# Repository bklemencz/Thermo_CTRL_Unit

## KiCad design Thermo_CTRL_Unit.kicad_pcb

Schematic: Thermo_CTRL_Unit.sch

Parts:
C1: 1u; C_0805
C2, C5, C7, C8, C9: 100n; C_0805
C3, C4: 22p; C_0805
C6: 10u; C_0805
C10, C13: 10uF; C_1206
C11: 100nF; C_0805
C12: 1uF; C_1206
D1, D2, D3: Red; LED_0805
D4: Green; LED_0805
D5: TL431; SOT-23
D6: SS13; SMA_Standard
FB1: FB_SMD_0805; R_0805
IC1: ATMEGA168PA-A; TQFP-32_7x7mm_Pitch0.8mm
J1: RJ12; RJ12_2mm_Pitch
P1: SW_TH1; JST_B3B-XH-A
P2: ISCP; Pin_Header_Straight_2x03
P3: SW_TH2; JST_B3B-XH-A
P4: TTL Sel; Pin_Header_Straight_1x03
P5: SW_TH3; JST_B3B-XH-A
P6: 3CH_ZCD_BRD; Pin_Header_Straight_1x06
P7: SW_TH4; JST_B3B-XH-A
P8: VIN; Pin_Header_Straight_1x02
P9: SW_SH; TerminalBlock_Pheonix_MKDS1.5-3pol
P10: IIC; Pin_Header_Straight_1x04
P11: SW_W1; JST_B2B-XH-A
P12: SW_W2; JST_B2B-XH-A
P13: SW_W3; JST_B2B-XH-A
P14: SW_W4; JST_B2B-XH-A
P15: CONN_01X05; Pin_Header_Straight_1x05
R1, R2, R3: 150; R_0805
R4, R5, R6, R7, R8, R9: 330; R_0805
R10: 120; R_0805
R11, R12, R13, R14, R16, R17, R18: 1K; R_0805
R15: 10k; R_0805
SW1: SW_PUSH; SW_SPST_TACT_SMD_3X6
U1: MAX487; SOIC-8_3.9x4.9mm_Pitch1.27mm
U2: MC78M05CDT; TO-252-2Lead
U3: HT7333-A; SOT89-3_Housing
X1: 16Mhz; crystal_smd_3225_4pin

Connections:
+3V3: C13.1, P10.1, U3.3
+5V: C1.1, C2.1, C11.1, C12.1, D4.1 (K), D6.2, FB1.1, IC1.4 (VCC), IC1.6 (VCC), J1.5, P1.1, P2.2, P3.1, P4.1, P5.1, P6.2, P7.1, P15.1, R4.1, R5.1, R6.1, R7.1, R8.1, R9.1, R15.1, U1.8 (VCC), U2.3, U3.2
/2V5_Ref: C8.1, D5.1 (K), D5.2 (Ref), IC1.20 (AREF), R16.2
/485_A: J1.3, R10.2, U1.6 (A/Y)
/485_B: J1.4, R10.1, U1.7 (B/Z)
/AVCC: C6.1, C7.1, FB1.2, IC1.18 (AVCC), R16.1
/DE: IC1.1 ((PCINT19/OC2B/INT1)PD3), P4.3
/DE_O: P4.2, U1.2 (/RE), U1.3 (DE)
/DTR: C9.1, P15.4
/MISO: IC1.16 ((PCINT4/MISO)PB4), P2.1
/MOSI: IC1.15 ((PCINT3/OC2A/MOSI)PB3), P2.4
/OSC1: C3.1, IC1.7 ((PCINT6/XTAL1/TOSC1)PB6), X1.1
/OSC2: C4.1, IC1.8 ((PCINT7/XTAL2/TOSC2)PB7), X1.3 (2)
/RST: C5.1, C9.2, IC1.29 ((PCINT14/~RESET~)PC6), P2.5, R15.2, SW1.1
/RxD: IC1.30 ((PCINT16/RXD)PD0), P15.2, U1.1 (RO)
/SCK: IC1.17 ((PCINT5/SCK)PB5), P2.3
/SCL: IC1.28 ((PCINT13/SCL/ADC5)PC5), P10.3
/SDA: IC1.27 ((PCINT12/SDA/ADC4)PC4), P10.4
/SW_SH1: IC1.25 ((PCINT10/ADC2)PC2), P9.1, R4.2
/SW_SH2: IC1.26 ((PCINT11/ADC3)PC3), P9.2, R5.2
/SW_W1: IC1.2 ((PCINT20/XCK/T0)PD4), P11.1, R6.2
/SW_W2: IC1.9 ((PCINT21/OC0B/T1)PD5), P12.1, R7.2
/SW_W3: IC1.10 ((PCINT22/OC0A/AIN0)PD6), P13.1, R8.2
/SW_W4: IC1.11 ((PCINT23/AIN1)PD7), P14.1, R9.2
/TH_1: IC1.23 ((PCINT8/ADC0)PC0), P1.2
/TH_2: IC1.24 ((PCINT9/ADC1)PC1), P3.2
/TH_3: IC1.19 (ADC6), P5.2, R18.1
/TH_4: IC1.22 (ADC7), P7.2, R17.1
/Triac_1: D1.1 (K), IC1.12 ((PCINT0/CLKO/ICP1)PB0), R3.2
/Triac_2: D2.1 (K), IC1.13 ((PCINT1/OC1A)PB1), R2.2
/Triac_3: D3.1 (K), IC1.14 ((PCINT2/OC1B/~SS~)PB2), R1.2
/TxD: IC1.31 ((PCINT17/TXD)PD1), P15.3, U1.4 (DI)
/VIN: C10.1, D6.1, P8.1, U2.1
/ZCD: IC1.32 ((PCINT18/INT0)PD2), P6.3
GND: C1.2, C2.2, C3.2, C4.2, C5.2, C6.2, C7.2, C8.2, C10.2, C11.2, C12.2, C13.2, D5.3 (A), IC1.3 (GND), IC1.5 (GND), IC1.21 (GND), J1.2, P1.3, P2.6, P3.3, P5.3, P6.1, P7.3, P8.2, P9.3, P10.2, P11.2, P12.2, P13.2, P14.2, P15.5, R11.2, R12.2, R13.2, R14.2, R17.2, R18.2, SW1.2, U1.5 (GND), U2.2, U3.1, X1.2 (case)
unnamed: D1.2 (A), R11.1
unnamed: D2.2 (A), R12.1
unnamed: D3.2 (A), R13.1
unnamed: D4.2 (A), R14.1
unnamed: P6.4, R1.1
unnamed: P6.5, R2.1
unnamed: P6.6, R3.1

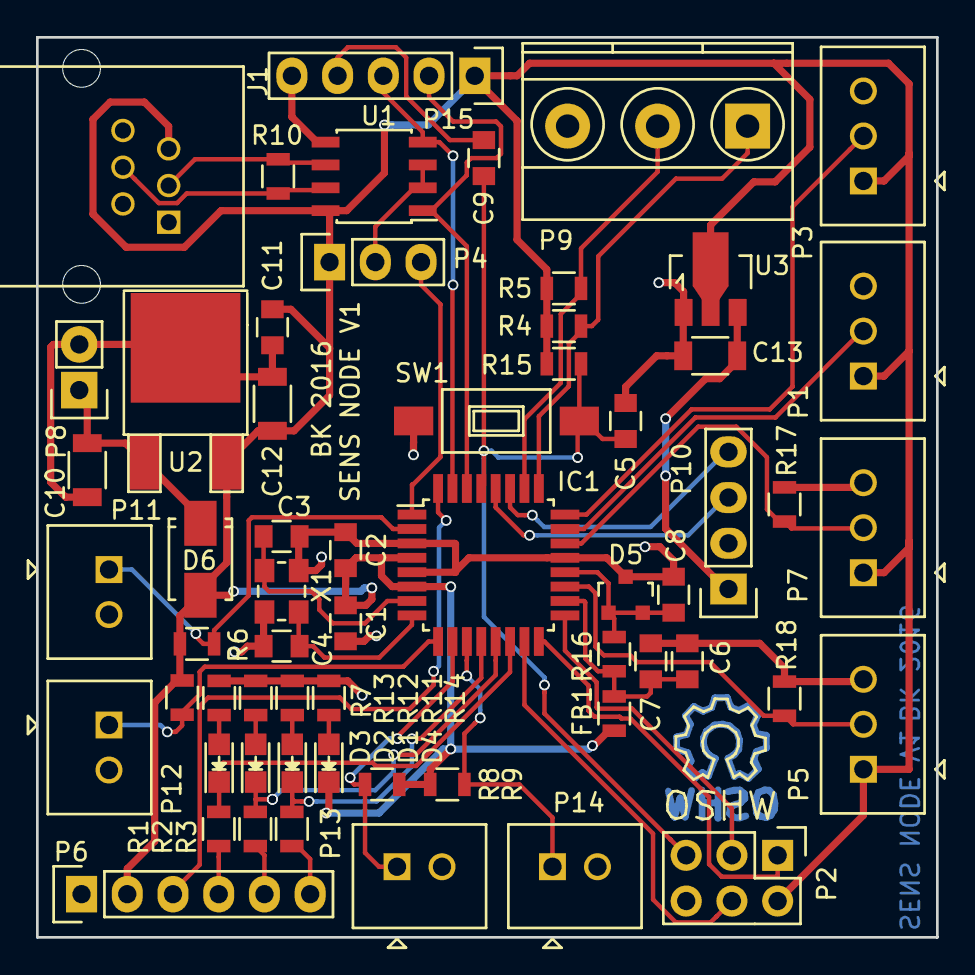
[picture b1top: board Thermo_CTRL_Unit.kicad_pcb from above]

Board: 2 copper layers, 50.0 x 50.0 mm, 60 parts (0 on the bottom side), 42 nets.

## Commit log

2016-03-16 :lollipop: Added .gitattributes & .gitignore files
2016-03-16 initial
2016-03-17 schematic update
2016-03-18 PCB STRT
2016-03-18 PCB Update
2016-03-23 SCH change
2016-03-23 PCB Change
